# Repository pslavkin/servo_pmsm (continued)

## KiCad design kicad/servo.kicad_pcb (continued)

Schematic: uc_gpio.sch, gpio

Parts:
U301: TMS320F28388DZWTS; BGA337CP80_19X19_1600X1600X140B50N; PartNumber TMS320F28388DZWTS

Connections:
1Wire_EN: U301.B14 (GPIO82); also elsewhere on the board
1Wire_IN: U301.A14 (GPIO81); also elsewhere on the board
1Wire_OUT: U301.C14 (GPIO83); also elsewhere on the board
BOOT1: U301.B16 (GPIO72); also elsewhere on the board
BOOT2: U301.A11 (GPIO84); also elsewhere on the board
BRK_A_MEC_C: U301.U13 (GPIO32); also elsewhere on the board
BRK_B_MEC_C: U301.T13 (GPIO33); also elsewhere on the board
CAN_RX: U301.T11 (GPIO30/CANA_RX); also elsewhere on the board
CAN_TX: U301.U11 (GPIO31/CANA_TX); also elsewhere on the board
DIR1: U301.C18 (GPIO68); also elsewhere on the board
DIR2: U301.A17 (GPIO70); also elsewhere on the board
ECAT0_RJ_LED0: U301.F18 (GPIO143/ESC_LED_LINK0_ACTIVE); also elsewhere on the board
ECAT0_RJ_LED1: U301.D14 (GPIO148/ESC_PHY0_LINKSTATUS); also elsewhere on the board
ECAT0_RX_CLK: U301.A8 (GPIO163/ESC_RX0_CLK); also elsewhere on the board
ECAT0_RX_D0: U301.C5 (GPIO165/ESC_RX0_DATA0); also elsewhere on the board
ECAT0_RX_D1: U301.D5 (GPIO166/ESC_RX0_DATA1); also elsewhere on the board
ECAT0_RX_D2: U301.C4 (GPIO167/ESC_RX0_DATA2); also elsewhere on the board
ECAT0_RX_D3: U301.D4 (GPIO168/ESC_RX0_DATA3); also elsewhere on the board
ECAT0_RX_DV: U301.D9 (GPIO162/ESC_RX0_DV); also elsewhere on the board
ECAT0_RX_ER: U301.B8 (GPIO164/ESC_RX0_ERR); also elsewhere on the board
ECAT0_TX_CLK: U301.B10 (GPIO157/ESC_TX0_CLK); also elsewhere on the board
ECAT0_TX_D0: U301.C10 (GPIO158/ESC_TX0_DATA0); also elsewhere on the board
ECAT0_TX_D1: U301.D10 (GPIO159/ESC_TX0_DATA1); also elsewhere on the board
ECAT0_TX_D2: U301.B9 (GPIO160/ESC_TX0_DATA2); also elsewhere on the board
ECAT0_TX_D3: U301.C9 (GPIO161/ESC_TX0_DATA3); also elsewhere on the board
ECAT0_TX_EN: U301.D12 (GPIO156/ESC_TX0_ENA); also elsewhere on the board
ECAT1_RJ_LED0: U301.F17 (GPIO144/ESC_LED_LINK1_ACTIVE); also elsewhere on the board
ECAT1_RJ_LED1: U301.A13 (GPIO149/ESC_PHY1_LINKSTATUS); also elsewhere on the board
ECAT1_RX_CLK: U301.T18 (GPIO137); also elsewhere on the board
ECAT1_RX_D0: U301.N19 (GPIO139); also elsewhere on the board
ECAT1_RX_D1: U301.M19 (GPIO140); also elsewhere on the board
ECAT1_RX_D2: U301.M18 (GPIO141); also elsewhere on the board
ECAT1_RX_D3: U301.L19 (GPIO142); also elsewhere on the board
ECAT1_RX_DV: U301.T17 (GPIO136); also elsewhere on the board
ECAT1_RX_ER: U301.T19 (GPIO138); also elsewhere on the board
ECAT1_TX_CLK: U301.U10 (GPIO130); also elsewhere on the board
ECAT1_TX_D0: U301.V10 (GPIO131); also elsewhere on the board
ECAT1_TX_D1: U301.W18 (GPIO132); also elsewhere on the board
ECAT1_TX_D2: U301.V18 (GPIO134); also elsewhere on the board
ECAT1_TX_D3: U301.U18 (GPIO135); also elsewhere on the board
ECAT1_TX_EN: U301.T10 (GPIO129); also elsewhere on the board
ECAT_EEPROM_SCL: U301.C13 (GPIO151/ESC_I2C_SCL); also elsewhere on the board
ECAT_EEPROM_SDA: U301.B13 (GPIO150/ESC_I2C_SDA); also elsewhere on the board
ECAT_LED_ERR: U301.E17 (GPIO145/ESC_LED_ERR); also elsewhere on the board
ECAT_LED_RUN: U301.D18 (GPIO146/ESC_LED_RUN); also elsewhere on the board
ECAT_MDCLK: U301.D13 (GPIO152/ESC_MDIO_CLK); also elsewhere on the board
ECAT_MDIO: U301.A12 (GPIO153/ESC_MDIO_DATA); also elsewhere on the board
ECAT_RST: U301.C12 (GPIO155/ESC_PHY_RESETn); also elsewhere on the board
ENDAT1_CLK: U301.M17 (GPIO60/SPIA_CLK); also elsewhere on the board
ENDAT1_CS: U301.L16 (GPIO61/SPIA_STEn); also elsewhere on the board
ENDAT1_MISO: U301.M16 (GPIO59/SPIA_SOMI); also elsewhere on the board
ENDAT1_MOSI: U301.N17 (GPIO58/SPIA_SIMO); also elsewhere on the board
ENDAT1_N_SKEW_CLK: U301.D2 (GPIO14/EPWM8A); also elsewhere on the board
ENDAT1_Y_SKEW_CLK: U301.D3 (GPIO15/EPWM8B); also elsewhere on the board
ENDAT2_CLK: U301.K16 (GPIO65/SPIB_CLK); also elsewhere on the board
ENDAT2_CS: U301.K17 (GPIO66/SPIB_STEn); also elsewhere on the board
ENDAT2_MISO: U301.L17 (GPIO64/SPIB_SOMI); also elsewhere on the board
ENDAT2_MOSI: U301.J16 (GPIO63/SPIB_SIMO); also elsewhere on the board
ENDAT2_N_SKEW_CLK: U301.E3 (GPIO18/EPWM10A); also elsewhere on the board
ENDAT2_Y_SKEW_CLK: U301.E4 (GPIO19/EPWM10B); also elsewhere on the board
ENET_CAT_XI: U301.B12 (GPIO154/ESC_PHY_CLK); also elsewhere on the board
ENET_COL: U301.M2 (GPIO110); also elsewhere on the board
ENET_CRS: U301.N2 (GPIO109); also elsewhere on the board
ENET_MDCLK: U301.J3 (GPIO105); also elsewhere on the board
ENET_MDIO: U301.L2 (GPIO106); also elsewhere on the board
ENET_PWDN: U301.L4 (GPIO108); also elsewhere on the board
ENET_RST: U301.T15 (GPIO119); also elsewhere on the board
ENET_RX_CLK: U301.M4 (GPIO111); also elsewhere on the board
ENET_RX_D0: U301.N3 (GPIO114); also elsewhere on the board
ENET_RX_D1: U301.V12 (GPIO115); also elsewhere on the board
ENET_RX_D2: U301.W10 (GPIO116); also elsewhere on the board
ENET_RX_D3: U301.U12 (GPIO117); also elsewhere on the board
ENET_RX_DV: U301.M3 (GPIO112); also elsewhere on the board
ENET_RX_ER: U301.N4 (GPIO113); also elsewhere on the board
ENET_TX_CLK: U301.U15 (GPIO120); also elsewhere on the board
ENET_TX_D0: U301.W16 (GPIO121); also elsewhere on the board
ENET_TX_D1: U301.T8 (GPIO122); also elsewhere on the board
ENET_TX_D2: U301.U8 (GPIO123); also elsewhere on the board
ENET_TX_D3: U301.V8 (GPIO124); also elsewhere on the board
ENET_TX_EN: U301.T12 (GPIO118); also elsewhere on the board
FAN_RPM1: U301.K18 (GPIO44); also elsewhere on the board
FAN_RPM2: U301.R16 (GPIO48); also elsewhere on the board
FLASH_SPI_CLK: U301.H3 (GPIO102/SPIC_CLK); also elsewhere on the board
FLASH_SPI_CS: U301.J1 (GPIO103/SPIC_STEn); also elsewhere on the board
FLASH_SPI_MISO: U301.H2 (GPIO101/SPIC_SOMI); also elsewhere on the board
FLASH_SPI_MOSI: U301.H1 (GPIO100/SPIC_SIMO); also elsewhere on the board
FREE_OUT_A1: U301.V17 (GPIO40); also elsewhere on the board
FREE_OUT_A2: U301.U17 (GPIO41); also elsewhere on the board
FREE_OUT_B1: U301.E19 (GPIO46); also elsewhere on the board
FREE_OUT_B2: U301.E18 (GPIO47); also elsewhere on the board
IGBT_ALARM1: U301.K19 (GPIO45); also elsewhere on the board
IGBT_ALARM2: U301.P17 (GPIO53); also elsewhere on the board
LCD_GPIO0: U301.C6 (GPIO88); also elsewhere on the board
LCD_GPIO1: U301.D11 (GPIO87); also elsewhere on the board
LCD_GPIO2: U301.C11 (GPIO86); also elsewhere on the board
LCD_GPIO3: U301.B11 (GPIO85); also elsewhere on the board
LCD_GPIO4: U301.B3 (GPIO95); also elsewhere on the board
LCD_GPIO5: U301.C3 (GPIO96); also elsewhere on the board
LCD_INT: U301.A5 (GPIO90); also elsewhere on the board
LCD_SPI_CLK: U301.B4 (GPIO93/SPID_CLK); also elsewhere on the board
LCD_SPI_CS: U301.A3 (GPIO94/SPID_STEn); also elsewhere on the board
LCD_SPI_MISO: U301.A4 (GPIO92/SPID_SOMI); also elsewhere on the board
LCD_SPI_MOSI: U301.B5 (GPIO91/SPID_SIMO); also elsewhere on the board
LCD_SPI_PDW: U301.D6 (GPIO89); also elsewhere on the board
PWM4SD_CLK: U301.E1 (GPIO16/EPWM9A); also elsewhere on the board
PWM_A_1H_C: U301.C8 (GPIO0/EPWM1A); also elsewhere on the board
PWM_A_1L_C: U301.D8 (GPIO1/EPWM1A); also elsewhere on the board
PWM_A_2H_C: U301.A7 (GPIO2/EPWM2A); also elsewhere on the board
PWM_A_2L_C: U301.B7 (GPIO3/EPWM2B); also elsewhere on the board
PWM_A_3H_C: U301.C7 (GPIO4/EPWM3A); also elsewhere on the board
PWM_A_3L_C: U301.D7 (GPIO5/EPWM3B); also elsewhere on the board
PWM_A_BRK_RES_C: U301.C2 (GPIO12/EPWM7A); also elsewhere on the board
PWM_B_1H_C: U301.A6 (GPIO6/EPWM4A); also elsewhere on the board
PWM_B_1L_C: U301.B6 (GPIO7/EPWM4B); also elsewhere on the board
PWM_B_2H_C: U301.G2 (GPIO8/EPWM5A); also elsewhere on the board
PWM_B_2L_C: U301.G3 (GPIO9/EPWM5B); also elsewhere on the board
PWM_B_3H_C: U301.B2 (GPIO10/EPWM6A); also elsewhere on the board
PWM_B_3L_C: U301.C1 (GPIO11/EPWM6B); also elsewhere on the board
PWM_B_BRK_RES_C: U301.D1 (GPIO13/EPWM7B); also elsewhere on the board
QEP1_A: U301.F2 (GPIO20/EQEP1_A); also elsewhere on the board
QEP1_B: U301.F3 (GPIO21/EQEP1_B); also elsewhere on the board
QEP1_I: U301.K4 (GPIO23/EQEP1_INDEX); also elsewhere on the board
QEP1_S: U301.J4 (GPIO22/EQEP1_STROBE); also elsewhere on the board
QEP2_A: U301.K3 (GPIO24/EQEP2_A); also elsewhere on the board
QEP2_B: U301.K2 (GPIO25/EQEP2_B); also elsewhere on the board
QEP2_I: U301.K1 (GPIO26/EQEP2_INDEX); also elsewhere on the board
QEP2_S: U301.L1 (GPIO27/EQEP2_STROBE); also elsewhere on the board
RS485_EN: U301.N16 (GPIO56); also elsewhere on the board
RS485_RX: U301.P19 (GPIO55/SCIB_RX); also elsewhere on the board
RS485_TX: U301.P18 (GPIO54/SCIB_TX); also elsewhere on the board
RUN_LED0: U301.U14 (GPIO34); also elsewhere on the board
RUN_LED1: U301.T14 (GPIO35); also elsewhere on the board
SCIA_RX: U301.V11 (GPIO28/SCIA_RX); also elsewhere on the board
SCIA_TX: U301.W11 (GPIO29/SCIA_TX); also elsewhere on the board
SD_A1: U301.V16 (GPIO36/SD1_D1); also elsewhere on the board
SD_A2: U301.U16 (GPIO37/SD1_D2); also elsewhere on the board
SD_A3: U301.T16 (GPIO38/SD1_D3); also elsewhere on the board
SD_A4: U301.W17 (GPIO39/SD1_D4); also elsewhere on the board
SD_A_CLK: U301.E2 (GPIO17/SD1_C1); also elsewhere on the board
SD_B1: U301.R17 (GPIO49/SD2_D1); also elsewhere on the board
SD_B2: U301.R18 (GPIO50/SD2_D2); also elsewhere on the board
SD_B3: U301.R19 (GPIO51/SD2_D3); also elsewhere on the board
SD_B4: U301.P16 (GPIO52/SD2_D4); also elsewhere on the board
SD_B_CLK: U301.N18 (GPIO57/SD2_C1); also elsewhere on the board
STEP1: U301.B19 (GPIO67); also elsewhere on the board
STEP2: U301.B18 (GPIO69); also elsewhere on the board
USB_D+: U301.C19 (GPIO43/USB0DP); also elsewhere on the board
USB_D-: U301.D19 (GPIO42/USB0DM); also elsewhere on the board

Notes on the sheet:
SD C2/3/4 goes directly inside uC only and MUST C1 required
one PWM channel for all 8 SD
Sdefault gpio's for sciA boot, don't move
SD C2/3/4 goes directly inside uC only and MUST C1 required
I've spend hours to choose the GPIO's for each interfase trying to not crash one to the other, just pay attemtion if you wanna move some pieces... I've used global labels connector to go from one page to another instead the off-page connector because it's more proune to errors.. I know that is not 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
uC GPIO's pins

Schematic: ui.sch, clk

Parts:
C1401: 1nF; C_0603_1608Metric
C1402, C1403, C1405: 10u; C_0603_1608Metric
C1404: 1uF; C_0603_1608Metric
D1401, D1402: red@2mA; LED_0603_1608Metric
J1401: NHD-4.3-480272FT-CTXL-T; HD-4.3-480272
J1402: Conn_01x02; Molex_KK-254_AE-6410-02A_1x02_P2.54mm_Vertical
R1401, R1402: 680; R_0603_1608Metric
R1403: 680e; R_0603_1608Metric
R1404: 220e; R_0603_1608Metric
SW1403, SW1404: SW_Push; SW_SPST_PTS645
U1401: PAM8301; SOT-23-6

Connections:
3V3: J1401.1, R1401.1, R1402.1; also elsewhere on the board
5VC: C1402.1, C1403.1, C1405.1, J1401.17, J1401.18, U1401.5 (VDD); also elsewhere on the board
GND: C1401.1, C1402.2 (Capacitor), C1403.2 (Capacitor), C1405.2 (Capacitor), J1401.2, J1401.19, J1401.20, SW1403.2, SW1404.2, U1401.2 (GND), U1401.4 (~SD); also elsewhere on the board
LCD_AUDIO: J1401.9, R1403.1; also elsewhere on the board
LCD_GPIO0: J1401.11; also elsewhere on the board
LCD_GPIO1: J1401.12; also elsewhere on the board
LCD_GPIO2: J1401.13; also elsewhere on the board
LCD_GPIO3: J1401.14; also elsewhere on the board
LCD_GPIO4: J1401.15, SW1403.1; also elsewhere on the board
LCD_GPIO5: J1401.16, SW1404.1; also elsewhere on the board
LCD_INT: J1401.7; also elsewhere on the board
LCD_SPI_CLK: J1401.3; also elsewhere on the board
LCD_SPI_CS: J1401.6; also elsewhere on the board
LCD_SPI_MISO: J1401.4; also elsewhere on the board
LCD_SPI_MOSI: J1401.5; also elsewhere on the board
LCD_SPI_PDW: J1401.8; also elsewhere on the board
unnamed: C1401.2 (Capacitor), R1403.2, R1404.1
unnamed: C1404.1, R1404.2
unnamed: C1404.2 (Capacitor), U1401.3 (IN)
unnamed: D1401.2 (A), R1401.2
unnamed: D1402.2 (A), R1402.2
unnamed: J1402.1, U1401.6 (OUT+)
unnamed: J1402.2, U1401.1 (OUT-)
RUN_LED0: D1401.1 (K); also elsewhere on the board
RUN_LED1: D1402.1 (K); also elsewhere on the board

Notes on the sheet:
Multipropouse LEDs
to optionally connect a speaker uggly instead of a buzzer
LCD UI interfase
interfase directly using f20 wires flat cable for NHD-4.3-480272FT-CTXL-T newheaven LCD or hand wiring EA eDIP128B-6LWTP or using any paralel 8080 3v3 interfase bitbanging the SPI and GPIO pins
backligth supply
I leave 4 push buttons as an alternative to touch pannel LCD, but also in case the some internal configuration has to be made without UI, or for debg. I think is not the best to use them as UI directly over the main board, for isolation and mechanicall isues.. better to do another board of leds and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
I leve a multi LCD/Touch/button 20 pins IDC connector to interfase with some UI. It could be simple leds,, a character LCD or an EVE graphic LCD as I recomment 'cause for same price you've all in one piece and it's already done, clean, usefull and intuitive interfase. I've added 2 more GPIO's 4 and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
for bulk capacitor

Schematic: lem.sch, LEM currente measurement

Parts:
C1501, C1502, C1509, C1513, C1514, C1515: 100pF; C_0603_1608Metric
C1504, C1505, C1508, C1510, C1511, C1512: 100nF; C_0603_1608Metric
J1501, J1502, J1503, J1504, J1505, J1506: tblock2x3; tblock02x03
R1501, R1503, R1505, R1507, R1509, R1511: 5k; R_0603_1608Metric
R1502, R1504, R1506, R1508, R1510, R1512: 3.3k; R_0603_1608Metric
U1501, U1502, U1503, U1504, U1505, U1506: LXS6-NPS; LEM_LTSR-NP

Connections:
5VC: C1504.2 (Capacitor), C1505.2 (Capacitor), C1508.2 (Capacitor), C1510.2 (Capacitor), C1511.2 (Capacitor), C1512.2 (Capacitor), U1501.9 (5V), U1502.9 (5V), U1503.9 (5V), U1504.9 (5V), U1505.9 (5V), U1506.9 (5V); also elsewhere on the board
/lem/LemAU_1: J1503.3, U1503.1 (IN1)
/lem/LemAU_2: J1503.5, U1503.2 (IN2)
/lem/LemAU_3: J1503.4, U1503.3 (IN3)
/lem/LemAU_4: J1503.1, U1503.4 (OUT4)
/lem/LemAU_5: J1503.2, U1503.5 (OUT5)
/lem/LemAU_6: J1503.6, U1503.6 (OUT6)
/lem/LemAV_1: J1501.3, U1501.1 (IN1)
/lem/LemAV_2: J1501.5, U1501.2 (IN2)
/lem/LemAV_3: J1501.4, U1501.3 (IN3)
/lem/LemAV_4: J1501.1, U1501.4 (OUT4)
/lem/LemAV_5: J1501.2, U1501.5 (OUT5)
/lem/LemAV_6: J1501.6, U1501.6 (OUT6)
/lem/LemA_All_1: J1502.3, U1502.1 (IN1)
/lem/LemA_All_2: J1502.5, U1502.2 (IN2)
/lem/LemA_All_3: J1502.4, U1502.3 (IN3)
/lem/LemA_All_4: J1502.1, U1502.4 (OUT4)
/lem/LemA_All_5: J1502.2, U1502.5 (OUT5)
/lem/LemA_All_6: J1502.6, U1502.6 (OUT6)
/lem/LemBU_1: J1504.3, U1504.1 (IN1)
/lem/LemBU_2: J1504.5, U1504.2 (IN2)
/lem/LemBU_3: J1504.4, U1504.3 (IN3)
/lem/LemBU_4: J1504.1, U1504.4 (OUT4)
/lem/LemBU_5: J1504.2, U1504.5 (OUT5)
/lem/LemBU_6: J1504.6, U1504.6 (OUT6)
/lem/LemBV_1: J1505.3, U1505.1 (IN1)
/lem/LemBV_2: J1505.5, U1505.2 (IN2)
/lem/LemBV_3: J1505.4, U1505.3 (IN3)
/lem/LemBV_4: J1505.1, U1505.4 (OUT4)
/lem/LemBV_5: J1505.2, U1505.5 (OUT5)
/lem/LemBV_6: J1505.6, U1505.6 (OUT6)
/lem/LemB_All_1: J1506.3, U1506.1 (IN1)
/lem/LemB_All_2: J1506.5, U1506.2 (IN2)
/lem/LemB_All_3: J1506.4, U1506.3 (IN3)
/lem/LemB_All_4: J1506.1, U1506.4 (OUT4)
/lem/LemB_All_5: J1506.2, U1506.5 (OUT5)
/lem/LemB_All_6: J1506.6, U1506.6 (OUT6)
GND: C1501.1, C1502.1, C1504.1, C1505.1, C1508.1, C1509.1, C1510.1, C1511.1, C1512.1, C1513.1, C1514.1, C1515.1, R1502.2, R1504.2, R1506.2, R1508.2, R1510.2, R1512.2, U1501.8 (GND), U1502.8 (GND), U1503.8 (GND), U1504.8 (GND), U1505.8 (GND), U1506.8 (GND); also elsewhere on the board
LEM_A_ALL: C1502.2 (Capacitor), R1503.2, R1504.1; also elsewhere on the board
LEM_A_U: C1509.2 (Capacitor), R1505.2, R1506.1; also elsewhere on the board
LEM_A_V: C1501.2 (Capacitor), R1501.2, R1502.1; also elsewhere on the board
LEM_B_ALL: C1515.2 (Capacitor), R1511.2, R1512.1; also elsewhere on the board
LEM_B_U: C1513.2 (Capacitor), R1507.2, R1508.1; also elsewhere on the board
LEM_B_V: C1514.2 (Capacitor), R1509.2, R1510.1; also elsewhere on the board
unnamed: R1501.1, U1501.7 (Out)
unnamed: R1503.1, U1502.7 (Out)
unnamed: R1505.1, U1503.7 (Out)
unnamed: R1507.1, U1504.7 (Out)
unnamed: R1509.1, U1505.7 (Out)
unnamed: R1511.1, U1506.7 (Out)

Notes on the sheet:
with 6 screw connector you could choose 3 range of current measurement 1x, 2x or 3x. IN 1 BRIDGE 1-2-3 and 4-5-6 OUT 4 ------- X IN 1 BRIDGE 1-2 and 3-5-6 OUT 4 ------- 2X IN 1 BRIDGE 2-6 and 3-5 OUT 4 ------- 3X
8 LEM's current measurement U+V+W+ALL x 2
The intention of these lems is to have the capacity on the control board to measure all the current, without the need of the sigma delta chips on power board side. Why?? becouse I've study the two options carrefullty and I've conclude that there are very similar, and more or less buck per byck (a l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
I've decided to eliminate 1 LEM, you could use 3 in line measurement, or 2 in line plus one for all. De reason is size of board and complexity
chanlog1: I've decided to return to a 2x3 terminal block output 'cause it match the size of the LEM

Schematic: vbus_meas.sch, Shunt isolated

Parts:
C1601, C1602, C1603, C1604, C1607, C1608, C1609, C1610: 100nF; C_0603_1608Metric
C1605, C1606: 330p; C_0603_1608Metric
L1601, L1602, L1603, L1604: L_Small; L_1206_3216Metric_Pad1.42x1.75mm_HandSolder
R1601, R1602, R1603, R1604, R1605, R1606: 12e; R_0603_1608Metric
R1607, R1608, R1609, R1610: 1k; R_0603_1608Metric
R1611, R1612, R1613, R1614, R1615, R1616, R1617, R1618: 1M; R_1206_3216Metric_Pad1.42x1.75mm_HandSolder
U1601, U1602: AMC1311B; SSO-8_6.8x5.9mm_P1.27mm_Clearance8mm
U1603, U1604: RFM-0505S; rfm0505

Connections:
3V3: C1603.2 (Capacitor), C1604.2 (Capacitor), U1601.8 (VDD2), U1602.8 (VDD2); also elsewhere on the board
5VH: L1603.1, L1604.1; also elsewhere on the board
GND: C1603.1, C1604.1, U1601.5 (GND2), U1602.5 (GND2); also elsewhere on the board
GNDH: C1609.1, C1610.1, U1603.1 (-VIN), U1604.1 (-VIN); also elsewhere on the board
unnamed: C1605.2 (Capacitor), R1605.1, U1601.2 (VIN_P)
unnamed: C1606.2 (Capacitor), R1606.1, U1602.2 (VIN_P)
unnamed: C1607.2 (Capacitor), L1601.2, R1607.1, U1601.1 (VDD1)
unnamed: C1608.2 (Capacitor), L1602.2, R1609.1, U1602.1 (VDD1)
unnamed: C1609.2 (Capacitor), L1603.2, U1603.2 (+VIN)
unnamed: C1610.2 (Capacitor), L1604.2, U1604.2 (+VIN)
unnamed: L1601.1, U1603.4 (+VOUT)
unnamed: L1602.1, U1604.4 (+VOUT)
unnamed: R1601.2, U1601.7 (VOUT_P)
unnamed: R1602.2, U1601.6 (VOUT_N)
unnamed: R1603.2, U1602.7 (VOUT_P)
unnamed: R1604.2, U1602.6 (VOUT_N)
unnamed: R1605.2, R1607.2, R1608.1, R1611.1, R1612.1
unnamed: R1606.2, R1609.2, R1610.1, R1614.1, R1615.1
unnamed: R1611.2, R1612.2, R1613.1, R1616.1
unnamed: R1614.2, R1615.2, R1617.1, R1618.1
VBUS_A_N: C1601.1, R1602.1; also elsewhere on the board
VBUS_A_N_H: C1605.1, C1607.1, R1608.2, U1601.3 (SHTDN), U1601.4 (GND1), U1603.3 (-VOUT); also elsewhere on the board
VBUS_A_P: C1601.2 (Capacitor), R1601.1; also elsewhere on the board
VBUS_A_P_H: R1613.2, R1616.2; also elsewhere on the board
VBUS_B_N: C1602.1, R1604.1; also elsewhere on the board
VBUS_B_N_H: C1606.1, C1608.1, R1610.2, U1602.3 (SHTDN), U1602.4 (GND1), U1604.3 (-VOUT); also elsewhere on the board
VBUS_B_P: C1602.2 (Capacitor), R1603.1; also elsewhere on the board
VBUS_B_P_H: R1617.2, R1618.2; also elsewhere on the board

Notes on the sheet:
VBUS -> R divider -> ISO ADC -> uC
It's an isolated specialized IC for volttage measurement that acept unipolar signal until 2V, so it has more dynamic range than AMC1301 for example
It's intended to measure the Vbus, one per motor, but they cold be joined if both motor share same VBus. The Vbus informatio will be used by the control algorith and to drive the break resistor PWM to protect the rise of the Vbus more than a threshold The input is expected not to be 220v or 380v. I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
if uou remove the isolated power supply, you loose the reinforced isolation. So it's bettar use that little and cheaper power supply
I've leave 2 for disipation porpouses and also for achive better precision

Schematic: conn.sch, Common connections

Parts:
J1701, J1702, J1703: NHD-4.3-480272FT-CTXL-T; IDC-Header_2x10_P2.54mm_Vertical
J1704, J1705: tblock2x13; IDC-Header_2x13_P2.54mm_Vertical

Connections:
1-WIREN_H: J1702.12, J1704.24, J1705.24; also elsewhere on the board
1-WIREP_H: J1702.11, J1704.23, J1705.23; also elsewhere on the board
5VH: J1701.1, J1702.1, J1703.1, J1704.1, J1705.1; also elsewhere on the board
15VH: J1701.2, J1702.2, J1703.2, J1704.2, J1705.2; also elsewhere on the board
BRK_A_MEC_H: J1701.18, J1704.18; also elsewhere on the board
BRK_B_MEC_H: J1703.18, J1705.18; also elsewhere on the board
FAN_RPM1_H: J1702.7, J1704.21; also elsewhere on the board
FAN_RPM2_H: J1702.8, J1705.21; also elsewhere on the board
FREE_OUT_A1_H: J1702.3, J1704.19; also elsewhere on the board
FREE_OUT_A2_H: J1702.5, J1704.20; also elsewhere on the board
FREE_OUT_B1_H: J1702.4, J1705.19; also elsewhere on the board
FREE_OUT_B2_H: J1702.6, J1705.20; also elsewhere on the board
GNDH: J1701.19, J1701.20, J1702.13, J1702.14, J1702.15, J1702.16, J1702.17, J1702.18, J1702.19, J1702.20, J1703.19, J1703.20, J1704.25, J1704.26, J1705.25, J1705.26; also elsewhere on the board
IGBT_ALARM1_H: J1702.9, J1704.22; also elsewhere on the board
IGBT_ALARM2_H: J1702.10, J1705.22; also elsewhere on the board
NTCA1_H: J1701.15, J1704.15; also elsewhere on the board
NTCA2_H: J1701.17, J1704.17; also elsewhere on the board
NTCB1_H: J1703.15, J1705.15; also elsewhere on the board
NTCB2_H: J1703.17, J1705.17; also elsewhere on the board
PWM4SD_A_CLK_H: J1701.13, J1704.13; also elsewhere on the board
PWM4SD_B_CLK_H: J1703.13, J1705.13; also elsewhere on the board
PWM_A_1H_H: J1701.4, J1704.4; also elsewhere on the board
PWM_A_1L_H: J1701.6, J1704.6; also elsewhere on the board
PWM_A_2H_H: J1701.8, J1704.8; also elsewhere on the board
PWM_A_2L_H: J1701.10, J1704.10; also elsewhere on the board
PWM_A_3H_H: J1701.12, J1704.12; also elsewhere on the board
PWM_A_3L_H: J1701.14, J1704.14; also elsewhere on the board
PWM_A_BRK_RES_H: J1701.16, J1704.16; also elsewhere on the board
PWM_B_1H_H: J1703.4, J1705.4; also elsewhere on the board
PWM_B_1L_H: J1703.6, J1705.6; also elsewhere on the board
PWM_B_2H_H: J1703.8, J1705.8; also elsewhere on the board
PWM_B_2L_H: J1703.10, J1705.10; also elsewhere on the board
PWM_B_3H_H: J1703.12, J1705.12; also elsewhere on the board
PWM_B_3L_H: J1703.14, J1705.14; also elsewhere on the board
PWM_B_BRK_RES_H: J1703.16, J1705.16; also elsewhere on the board
SD_A1_H: J1701.3, J1704.3; also elsewhere on the board
SD_A2_H: J1701.5, J1704.5; also elsewhere on the board
SD_A3_H: J1701.7, J1704.7; also elsewhere on the board
SD_A4_H: J1701.9, J1704.9; also elsewhere on the board
SD_A_CLK_H: J1701.11, J1704.11; also elsewhere on the board
SD_B1_H: J1703.3, J1705.3; also elsewhere on the board
SD_B2_H: J1703.5, J1705.5; also elsewhere on the board
SD_B3_H: J1703.7, J1705.7; also elsewhere on the board
SD_B4_H: J1703.9, J1705.9; also elsewhere on the board
SD_B_CLK_H: J1703.11, J1705.11; also elsewhere on the board

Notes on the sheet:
Common Connections
Free to use until now

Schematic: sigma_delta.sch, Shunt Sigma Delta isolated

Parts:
C1801, C1802, C1803, C1804, C1805, C1806, C1807, C1808, C1809, C1810, C1811, C1812, C1813, C1814, C1815, C1816, C1817, C1818: 100pF; C_0603_1608Metric
R1801, R1802, R1803, R1804, R1805, R1806, R1807, R1808, R1809, R1810, R1811, R1812: 10e; R_0603_1608Metric
U1801, U1802: SI8661BD; SOIC-16W_7.5x10.3mm_P1.27mm
U1803, U1804: SN74LVC2G17DBVR; SOT-23-6

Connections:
3V3: C1813.1, C1818.1, U1801.16 (VCC2), U1802.16 (VCC2); also elsewhere on the board
5VH: C1814.1, C1815.1, C1816.1, C1817.1, U1801.1 (VCC1), U1802.1 (VCC1), U1803.5 (VCC), U1804.5 (VCC); also elsewhere on the board
GND: C1813.2 (Capacitor), C1818.2 (Capacitor), U1801.9 (GND2), U1802.9 (GND2); also elsewhere on the board
GNDH: C1801.2 (Capacitor), C1802.2 (Capacitor), C1803.2 (Capacitor), C1804.2 (Capacitor), C1805.2 (Capacitor), C1806.2 (Capacitor), C1807.2 (Capacitor), C1808.2 (Capacitor), C1809.2 (Capacitor), C1810.2 (Capacitor), C1811.2 (Capacitor), C1812.2 (Capacitor), C1814.2 (Capacitor), C1815.2 (Capacitor), C1816.2 (Capacitor), C1817.2 (Capacitor), U1801.8 (GND1), U1802.8 (GND1), U1803.2 (GND), U1804.2 (GND); also elsewhere on the board
unnamed: C1801.1, R1802.1, U1801.2 (A1)
unnamed: C1802.1, R1803.1, U1801.3 (A2)
unnamed: C1803.1, R1804.1, U1801.4 (A3)
unnamed: C1804.1, R1805.1, U1801.5 (A4)
unnamed: C1805.1, R1806.1, U1803.3 (2A)
unnamed: C1808.1, R1811.1, U1804.3 (2A)
unnamed: C1809.1, R1810.1, U1802.5 (A4)
unnamed: C1810.1, R1809.1, U1802.4 (A3)
unnamed: C1811.1, R1808.1, U1802.3 (A2)
unnamed: C1812.1, R1807.1, U1802.2 (A1)
unnamed: R1801.1, U1803.6 (1Y)
unnamed: R1812.1, U1804.6 (1Y)
unnamed: U1801.6 (A5), U1803.4 (2Y)
unnamed: U1801.7 (A6), U1803.1 (1A)
unnamed: U1802.6 (A5), U1804.4 (2Y)
unnamed: U1802.7 (A6), U1804.1 (1A)
PWM4SD_A_CLK_H: C1806.1, R1801.2; also elsewhere on the board
PWM4SD_B_CLK_H: C1807.1, R1812.2; also elsewhere on the board
PWM4SD_CLK: U1801.10 (B6), U1802.10 (B6); also elsewhere on the board
SD_A1: U1801.15 (B1); also elsewhere on the board
SD_A1_H: R1802.2; also elsewhere on the board
SD_A2: U1801.14 (B2); also elsewhere on the board
SD_A2_H: R1803.2; also elsewhere on the board
SD_A3: U1801.13 (B3); also elsewhere on the board
SD_A3_H: R1804.2; also elsewhere on the board
SD_A4: U1801.12 (B4); also elsewhere on the board
SD_A4_H: R1805.2; also elsewhere on the board
SD_A_CLK: U1801.11 (B5); also elsewhere on the board
SD_A_CLK_H: R1806.2; also elsewhere on the board
SD_B1: U1802.15 (B1); also elsewhere on the board
SD_B1_H: R1807.2; also elsewhere on the board
SD_B2: U1802.14 (B2); also elsewhere on the board
SD_B2_H: R1808.2; also elsewhere on the board
SD_B3: U1802.13 (B3); also elsewhere on the board
SD_B3_H: R1809.2; also elsewhere on the board
SD_B4: U1802.12 (B4); also elsewhere on the board
SD_B4_H: R1810.2; also elsewhere on the board
SD_B_CLK: U1802.11 (B5); also elsewhere on the board
SD_B_CLK_H: R1811.2; also elsewhere on the board

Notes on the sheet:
Isolated sigma delta ADC
Choose a package pin-to-pin compatible with TI ISO7761. But SIlabs cost halt the price as TI
It's intended for power board circuitery to supply all the signals to control board. The control board will use the SD filter to aquire the data. All the power part will be at power board. PWM clk output to powerboard and then come back again to maintain delays with resect to SD data channels. On p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

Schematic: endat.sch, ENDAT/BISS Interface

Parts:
C1901, C1904, C1905, C1910, C1913, C1914: 100nF; C_0603_1608Metric
J1901: tblock2x6; tblock02x6_3.81
JP1901: jumper; SolderJumper-3_P1.3mm_Open_RoundedPad1.0x1.5mm
R1901, R1932: 0e; R_0603_1608Metric
R1902, R1931: 0e(dnp); R_0603_1608Metric
R1903, R1905, R1906, R1908, R1911, R1913, R1914, R1916: 10k; R_0603_1608Metric
R1904, R1907, R1912, R1915: 1k; R_0603_1608Metric
U1901, U1908: SI8662BD; SOIC-16W_7.5x10.3mm_P1.27mm
U1904, U1905: SN75C1168DBR; SOIC-16W_5.3x10.2mm_P1.27mm

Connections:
3V3: C1901.2 (Capacitor), C1914.2 (Capacitor), U1901.1 (VCC1), U1908.1 (VCC1); also elsewhere on the board
5VH: C1904.2 (Capacitor), C1905.2 (Capacitor), C1910.2 (Capacitor), C1913.2 (Capacitor), JP1901.1 (A), R1903.1, R1906.1, R1911.1, R1914.1, U1901.16 (VCC2), U1904.12 (2DE), U1904.16 (VCC), U1905.12 (2DE), U1905.16 (VCC), U1908.16 (VCC2); also elsewhere on the board
15VH: JP1901.3 (B); also elsewhere on the board
/endat/ENDAT1_CLK_H: U1901.12 (B4), U1904.9 (2D)
/endat/ENDAT1_CS_H: U1901.13 (B3), U1904.4 (1DE)
/endat/ENDAT1_MISO_H: U1901.11 (B5), U1904.3 (1R)
/endat/ENDAT1_MOSI_H: U1901.15 (B1), U1904.15 (1D)
/endat/ENDAT2_CLK_H: U1905.9 (2D), U1908.12 (B4)
/endat/ENDAT2_CS_H: U1905.4 (1DE), U1908.13 (B3)
/endat/ENDAT2_MISO_H: U1905.3 (1R), U1908.11 (B5)
/endat/ENDAT2_MOSI_H: U1905.15 (1D), U1908.15 (B1)
ENDAT1_CLK: R1901.1; also elsewhere on the board
ENDAT1_CS: U1901.4 (A3); also elsewhere on the board
ENDAT1_MISO: U1901.6 (A5); also elsewhere on the board
ENDAT1_MOSI: U1901.2 (A1); also elsewhere on the board
ENDAT1_N_SKEW_CLK: R1902.2, U1901.5 (A4); also elsewhere on the board
ENDAT1_Y_SKEW_CLK: R1901.2, R1902.1; also elsewhere on the board
ENDAT2_CLK: R1932.1; also elsewhere on the board
ENDAT2_CS: U1908.4 (A3); also elsewhere on the board
ENDAT2_MISO: U1908.6 (A5); also elsewhere on the board
ENDAT2_MOSI: U1908.2 (A1); also elsewhere on the board
ENDAT2_N_SKEW_CLK: R1931.2, U1908.5 (A4); also elsewhere on the board
ENDAT2_Y_SKEW_CLK: R1931.1, R1932.2; also elsewhere on the board
GND: C1901.1, C1914.1, U1901.8 (GND1), U1908.8 (GND1); also elsewhere on the board
GNDH: C1904.1, C1905.1, C1910.1, C1913.1, J1901.6a, J1901.6b, R1905.2, R1908.2, R1913.2, R1916.2, U1901.9 (GND2), U1904.8 (GND), U1905.8 (GND), U1908.9 (GND2); also elsewhere on the board
unnamed: J1901.1a, J1901.1b, JP1901.2 (C)
unnamed: J1901.2a, R1911.2, R1912.1, U1904.1 (~1B), U1904.14 (1Y)
unnamed: J1901.2b, R1906.2, R1907.1, U1905.1 (~1B), U1905.14 (1Y)
unnamed: J1901.3a, R1912.2, R1913.1, U1904.2 (1A), U1904.13 (~1Z)
unnamed: J1901.3b, R1907.2, R1908.1, U1905.2 (1A), U1905.13 (~1Z)
unnamed: J1901.4a, R1914.2, R1915.1, U1904.11 (~2Z)
unnamed: J1901.4b, R1903.2, R1904.1, U1905.11 (~2Z)
unnamed: J1901.5a, R1915.2, R1916.1, U1904.10 (2Y)
unnamed: J1901.5b, R1904.2, R1905.1, U1905.10 (2Y)

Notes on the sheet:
2X Isolated diferential ENDAT interface
free to use
to choose between the spi clk out directly (useless for endat) or to send a PWM clk and its pair acting as skewed spi clk input to the spi uC delayed and the SPI playing as a slave... very strange, but it's a way to manage the badly designed endat...

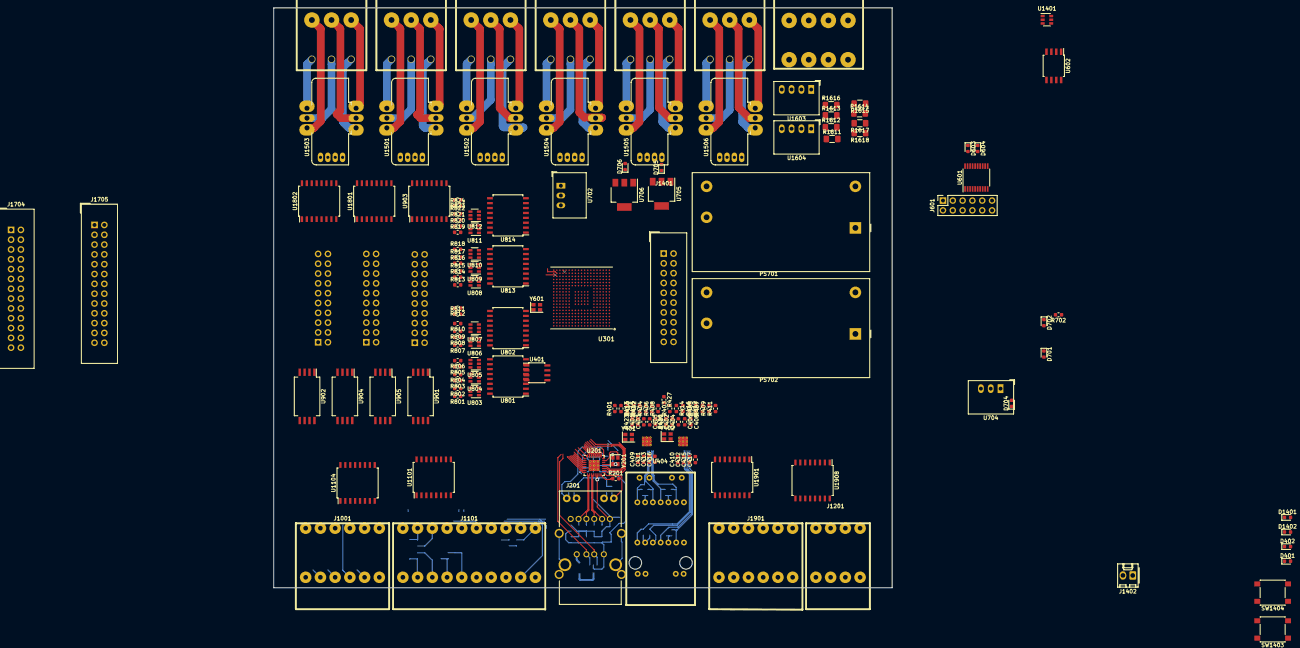
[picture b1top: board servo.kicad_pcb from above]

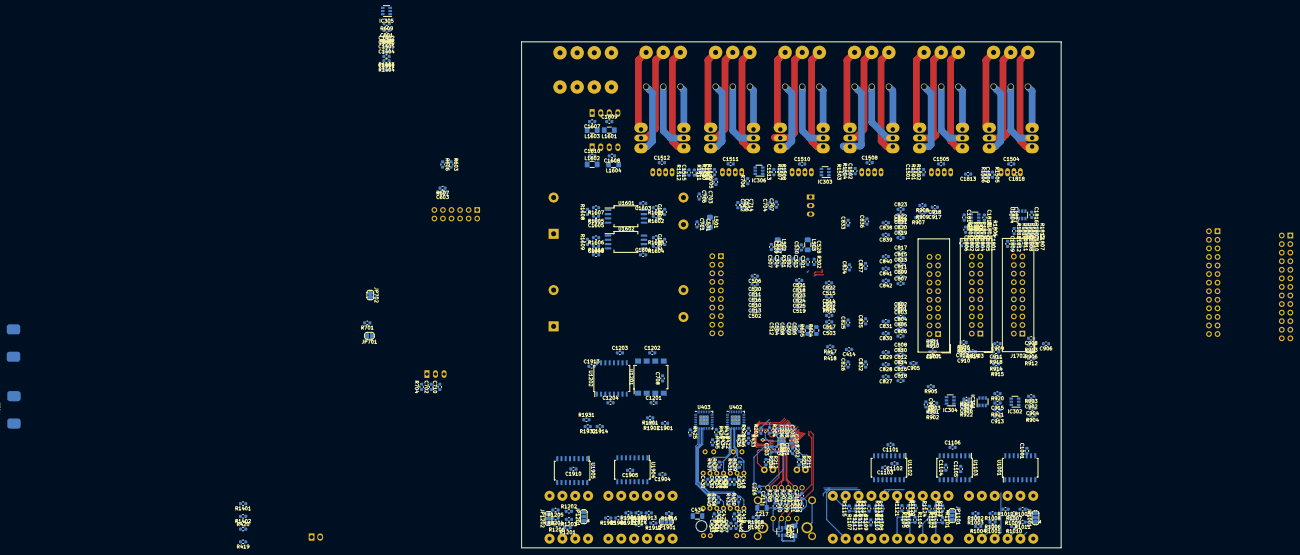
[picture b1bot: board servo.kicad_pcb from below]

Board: 6 copper layers, 160.0 x 150.0 mm, 563 parts (414 on the bottom side), 492 nets.

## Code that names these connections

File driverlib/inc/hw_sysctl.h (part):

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// The following are defines for the bit fields in the GPIOLPMSEL0 register
//
//*****************************************************************************
#define SYSCTL_GPIOLPMSEL0_GPIO0  0x1U         // GPIO0 Enable for LPM Wakeup
#define SYSCTL_GPIOLPMSEL0_GPIO1  0x2U         // GPIO1 Enable for LPM Wakeup
#define SYSCTL_GPIOLPMSEL0_GPIO2  0x4U         // GPIO2 Enable for LPM Wakeup
#define SYSCTL_GPIOLPMSEL0_GPIO3  0x8U         // GPIO3 Enable for LPM Wakeup
#define SYSCTL_GPIOLPMSEL0_GPIO4  0x10U        // GPIO4 Enable for LPM Wakeup
#define SYSCTL_GPIOLPMSEL0_GPIO5  0x20U        // GPIO5 Enable for LPM Wakeup
#define SYSCTL_GPIOLPMSEL0_GPIO6  0x40U        // GPIO6 Enable for LPM Wakeup
#define SYSCTL_GPIOLPMSEL0_GPIO7  0x80U        // GPIO7 Enable for LPM Wakeup
#define SYSCTL_GPIOLPMSEL0_GPIO8  0x100U       // GPIO8 Enable for LPM Wakeup
#define SYSCTL_GPIOLPMSEL0_GPIO9  0x200U       // GPIO9 Enable for LPM Wakeup
#define SYSCTL_GPIOLPMSEL0_GPIO10  0x400U       // GPIO10 Enable for LPM Wakeup
#define SYSCTL_GPIOLPMSEL0_GPIO11  0x800U       // GPIO11 Enable for LPM Wakeup
#define SYSCTL_GPIOLPMSEL0_GPIO12  0x1000U      // GPIO12 Enable for LPM Wakeup
#define SYSCTL_GPIOLPMSEL0_GPIO13  0x2000U      // GPIO13 Enable for LPM Wakeup
#define SYSCTL_GPIOLPMSEL0_GPIO14  0x4000U      // GPIO14 Enable for LPM Wakeup
#define SYSCTL_GPIOLPMSEL0_GPIO15  0x8000U      // GPIO15 Enable for LPM Wakeup
#define SYSCTL_GPIOLPMSEL0_GPIO16  0x10000U     // GPIO16 Enable for LPM Wakeup
#define SYSCTL_GPIOLPMSEL0_GPIO17  0x20000U     // GPIO17 Enable for LPM Wakeup
#define SYSCTL_GPIOLPMSEL0_GPIO18  0x40000U     // GPIO18 Enable for LPM Wakeup
#define SYSCTL_GPIOLPMSEL0_GPIO19  0x80000U     // GPIO19 Enable for LPM Wakeup
#define SYSCTL_GPIOLPMSEL0_GPIO20  0x100000U    // GPIO20 Enable for LPM Wakeup
#define SYSCTL_GPIOLPMSEL0_GPIO21  0x200000U    // GPIO21 Enable for LPM Wakeup
#define SYSCTL_GPIOLPMSEL0_GPIO22  0x400000U    // GPIO22 Enable for LPM Wakeup
#define SYSCTL_GPIOLPMSEL0_GPIO23  0x800000U    // GPIO23 Enable for LPM Wakeup
#define SYSCTL_GPIOLPMSEL0_GPIO24  0x1000000U   // GPIO24 Enable for LPM Wakeup
#define SYSCTL_GPIOLPMSEL0_GPIO25  0x2000000U   // GPIO25 Enable for LPM Wakeup
#define SYSCTL_GPIOLPMSEL0_GPIO26  0x4000000U   // GPIO26 Enable for LPM Wakeup
#define SYSCTL_GPIOLPMSEL0_GPIO27  0x8000000U   // GPIO27 Enable for LPM Wakeup
#define SYSCTL_GPIOLPMSEL0_GPIO28  0x10000000U  // GPIO28 Enable for LPM Wakeup
#define SYSCTL_GPIOLPMSEL0_GPIO29  0x20000000U  // GPIO29 Enable for LPM Wakeup
#define SYSCTL_GPIOLPMSEL0_GPIO30  0x40000000U  // GPIO30 Enable for LPM Wakeup
#define SYSCTL_GPIOLPMSEL0_GPIO31  0x80000000U  // GPIO31 Enable for LPM Wakeup

//*****************************************************************************
//
// The following are defines for the bit fields in the GPIOLPMSEL1 register
//
//*****************************************************************************
#define SYSCTL_GPIOLPMSEL1_GPIO32  0x1U         // GPIO32 Enable for LPM Wakeup
#define SYSCTL_GPIOLPMSEL1_GPIO33  0x2U         // GPIO33 Enable for LPM Wakeup
#define SYSCTL_GPIOLPMSEL1_GPIO34  0x4U         // GPIO34 Enable for LPM Wakeup
#define SYSCTL_GPIOLPMSEL1_GPIO35  0x8U         // GPIO35 Enable for LPM Wakeup
#define SYSCTL_GPIOLPMSEL1_GPIO36  0x10U        // GPIO36 Enable for LPM Wakeup
#define SYSCTL_GPIOLPMSEL1_GPIO37  0x20U        // GPIO37 Enable for LPM Wakeup
#define SYSCTL_GPIOLPMSEL1_GPIO38  0x40U        // GPIO38 Enable for LPM Wakeup
#define SYSCTL_GPIOLPMSEL1_GPIO39  0x80U        // GPIO39 Enable for LPM Wakeup
#define SYSCTL_GPIOLPMSEL1_GPIO40  0x100U       // GPIO40 Enable for LPM Wakeup
#define SYSCTL_GPIOLPMSEL1_GPIO41  0x200U       // GPIO41 Enable for LPM Wakeup
#define SYSCTL_GPIOLPMSEL1_GPIO42  0x400U       // GPIO42 Enable for LPM Wakeup
#define SYSCTL_GPIOLPMSEL1_GPIO43  0x800U       // GPIO43 Enable for LPM Wakeup
#define SYSCTL_GPIOLPMSEL1_GPIO44  0x1000U      // GPIO44 Enable for LPM Wakeup
#define SYSCTL_GPIOLPMSEL1_GPIO45  0x2000U      // GPIO45 Enable for LPM Wakeup
#define SYSCTL_GPIOLPMSEL1_GPIO46  0x4000U      // GPIO46 Enable for LPM Wakeup
#define SYSCTL_GPIOLPMSEL1_GPIO47  0x8000U      // GPIO47 Enable for LPM Wakeup
#define SYSCTL_GPIOLPMSEL1_GPIO48  0x10000U     // GPIO48 Enable for LPM Wakeup
#define SYSCTL_GPIOLPMSEL1_GPIO49  0x20000U     // GPIO49 Enable for LPM Wakeup
#define SYSCTL_GPIOLPMSEL1_GPIO50  0x40000U     // GPIO50 Enable for LPM Wakeup
#define SYSCTL_GPIOLPMSEL1_GPIO51  0x80000U     // GPIO51 Enable for LPM Wakeup
#define SYSCTL_GPIOLPMSEL1_GPIO52  0x100000U    // GPIO52 Enable for LPM Wakeup
#define SYSCTL_GPIOLPMSEL1_GPIO53  0x200000U    // GPIO53 Enable for LPM Wakeup
#define SYSCTL_GPIOLPMSEL1_GPIO54  0x400000U    // GPIO54 Enable for LPM Wakeup
#define SYSCTL_GPIOLPMSEL1_GPIO55  0x800000U    // GPIO55 Enable for LPM Wakeup
#define SYSCTL_GPIOLPMSEL1_GPIO56  0x1000000U   // GPIO56 Enable for LPM Wakeup
#define SYSCTL_GPIOLPMSEL1_GPIO57  0x2000000U   // GPIO57 Enable for LPM Wakeup
#define SYSCTL_GPIOLPMSEL1_GPIO58  0x4000000U   // GPIO58 Enable for LPM Wakeup
#define SYSCTL_GPIOLPMSEL1_GPIO59  0x8000000U   // GPIO59 Enable for LPM Wakeup
#define SYSCTL_GPIOLPMSEL1_GPIO60  0x10000000U  // GPIO60 Enable for LPM Wakeup
#define SYSCTL_GPIOLPMSEL1_GPIO61  0x20000000U  // GPIO61 Enable for LPM Wakeup
#define SYSCTL_GPIOLPMSEL1_GPIO62  0x40000000U  // GPIO62 Enable for LPM Wakeup
#define SYSCTL_GPIOLPMSEL1_GPIO63  0x80000000U  // GPIO63 Enable for LPM Wakeup

//*****************************************************************************
//
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
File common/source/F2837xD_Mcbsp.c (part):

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
    //
    // MDXA
    // GPIO20
    // GPIO84
    //
    GpioCtrlRegs.GPAMUX2.bit.GPIO20 = 2;
    //GpioCtrlRegs.GPCGMUX2.bit.GPIO84 = 3;
    //GpioCtrlRegs.GPCMUX2.bit.GPIO84 = 3;

    //
    // MDRA
    // GPIO21 with asynchronous qualification
    // GPIO85 with asynchronous qualification
    //
    GpioCtrlRegs.GPAMUX2.bit.GPIO21 = 2;
    GpioCtrlRegs.GPAQSEL2.bit.GPIO21 = 3;
    //GpioCtrlRegs.GPCGMUX2.bit.GPIO85 = 3;
    //GpioCtrlRegs.GPCMUX2.bit.GPIO85 = 3;
    //GpioCtrlRegs.GPCQSEL2.bit.GPIO85 = 3;

    //
    // MCLKXA
    // GPIO22 with asynchronous qualification
    // GPIO86 with asynchronous qualification
    //
    GpioCtrlRegs.GPAMUX2.bit.GPIO22 = 2;
    //GpioCtrlRegs.GPAQSEL2.bit.GPIO22 = 3;
    //GpioCtrlRegs.GPCGMUX2.bit.GPIO86 = 3;
    //GpioCtrlRegs.GPCMUX2.bit.GPIO86 = 3;
    //GpioCtrlRegs.GPCQSEL2.bit.GPIO86 = 3;

    //
    // MCLKRA
    // Select one of the following
    // GPIO7 with asynchronous qualification
    // GPIO58 with asynchronous qualification
    //
    GpioCtrlRegs.GPAMUX1.bit.GPIO7 = 2;
    GpioCtrlRegs.GPAQSEL1.bit.GPIO7 = 3;
    //GpioCtrlRegs.GPBMUX2.bit.GPIO58 = 1;
    //GpioCtrlRegs.GPBQSEL2.bit.GPIO58 = 3;

    //
    // MFSXA
    // GPIO23 with asynchronous qualification
    // GPIO87 with asynchronous qualification
    //
    GpioCtrlRegs.GPAMUX2.bit.GPIO23 = 2;
    //GpioCtrlRegs.GPAQSEL2.bit.GPIO23 = 3;
    //GpioCtrlRegs.GPCGMUX2.bit.GPIO87 = 3;
    //GpioCtrlRegs.GPCMUX2.bit.GPIO87 = 3;
    //GpioCtrlRegs.GPCQSEL2.bit.GPIO87 = 3;

    //
    // MFSRA
    // Select one of the following
    // GPIO5 with asynchronous qualification
    // GPIO59 with asynchronous qualification
    //
    GpioCtrlRegs.GPAMUX1.bit.GPIO5 = 2;
    GpioCtrlRegs.GPAQSEL1.bit.GPIO5 = 3;
    //GpioCtrlRegs.GPBMUX2.bit.GPIO59 = 1;
    //GpioCtrlRegs.GPBQSEL2.bit.GPIO59 = 3;

    EDIS;
#endif
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
    //
    // Select one of the following for MDXB
    // GPIO24
    // GPIO84
    //
    //GpioCtrlRegs.GPAMUX2.bit.GPIO24 = 3;
    GpioCtrlRegs.GPCGMUX2.bit.GPIO84 = 1;
    GpioCtrlRegs.GPCMUX2.bit.GPIO84 = 2;

    //
    // MDRB
    // GPIO13 with asynchronous qualification
    // GPIO25 with asynchronous qualification
    // GPIO85 with asynchronous qualification
    //
    //GpioCtrlRegs.GPAMUX1.bit.GPIO13 = 3;
    //GpioCtrlRegs.GPAQSEL1.bit.GPIO13 = 3;
    //GpioCtrlRegs.GPAMUX2.bit.GPIO25 = 3;
    //GpioCtrlRegs.GPAQSEL2.bit.GPIO25 = 3;
    GpioCtrlRegs.GPCGMUX2.bit.GPIO85 = 1;
    GpioCtrlRegs.GPCMUX2.bit.GPIO85 = 2;
    GpioCtrlRegs.GPCQSEL2.bit.GPIO85 = 3;

    //
    // MCLKXB
    // GPIO14 with asynchronous qualification
    // GPIO26 with asynchronous qualification
    // GPIO86 with asynchronous qualification
    //
    //GpioCtrlRegs.GPAMUX1.bit.GPIO14 = 3;
    //GpioCtrlRegs.GPAQSEL1.bit.GPIO14 = 3;
    //GpioCtrlRegs.GPAMUX2.bit.GPIO26 = 3;
    //GpioCtrlRegs.GPAQSEL2.bit.GPIO26 = 3;
    GpioCtrlRegs.GPCGMUX2.bit.GPIO86 = 1;
    GpioCtrlRegs.GPCMUX2.bit.GPIO86 = 2;
    GpioCtrlRegs.GPCQSEL2.bit.GPIO86= 3;

    //
    // MCLKRB
    // Select one of the following
    // GPIO3 with asynchronous qualification
    // GPIO60 with asynchronous qualification
    //
    //GpioCtrlRegs.GPAMUX1.bit.GPIO3 = 3;
    //GpioCtrlRegs.GPAQSEL1.bit.GPIO3 = 3;
    GpioCtrlRegs.GPBMUX2.bit.GPIO60 = 1;
    GpioCtrlRegs.GPBQSEL2.bit.GPIO60 = 3;

    //
    // MFSXB
    // GPIO15 with asynchronous qualification
    // GPIO27 with asynchronous qualification
    // GPIO87 with asynchronous qualification
    //
    //GpioCtrlRegs.GPAMUX1.bit.GPIO15 = 3;
    //GpioCtrlRegs.GPAQSEL1.bit.GPIO15 = 3;
    //GpioCtrlRegs.GPAMUX2.bit.GPIO27 = 3;
    //GpioCtrlRegs.GPAQSEL2.bit.GPIO27 = 3;
    GpioCtrlRegs.GPCGMUX2.bit.GPIO87 = 1;
    GpioCtrlRegs.GPCMUX2.bit.GPIO87 = 2;
    GpioCtrlRegs.GPCQSEL2.bit.GPIO87= 3;

    //
    // MFSRB
    // Select one of the following
    // GPIO1 with asynchronous qualification
    // GPIO61 with asynchronous qualification
    //
    //GpioCtrlRegs.GPAMUX1.bit.GPIO1 = 3;
    //GpioCtrlRegs.GPAQSEL1.bit.GPIO1 = 3;
    GpioCtrlRegs.GPBMUX2.bit.GPIO61 = 1;
    GpioCtrlRegs.GPBQSEL2.bit.GPIO61 = 3;

    EDIS;

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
